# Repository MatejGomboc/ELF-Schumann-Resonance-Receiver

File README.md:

# ELARA -- ELF Atmospheric Radio Analyser

A professional-grade electric-field receiver for natural ELF radio signals
(1--50 Hz), optimised for Schumann resonance monitoring with exceptional
sensitivity. Inspired by [Renato Romero's](http://www.vlf.it/cumiana/livedata.html)
electric-field receiver work, engineered for dramatically better noise
performance using modern electrometer-grade components.

## Architecture

The system is deliberately simplified: the only custom PCB is the outdoor
antenna unit. The indoor side is entirely off-the-shelf.

- **Marconi T-antenna** (~10 m vertical, ~15 m capacitive top, ~140 pF)
- **Outdoor unit** -- single custom PCB inside a compartmentalised ALU EM shield,
  housed in a weatherproof plastic enclosure, with a separate two-bucket PSU box
  and, on mains, a 30 W thermostat box heater that keeps the ADC within its rating
  in winter; the box stands on a stiff steel post at the foot of the down-lead under
  a white aluminium sun and rain roof on its own arms
- **Indoor unit** -- any USB audio interface with an AES3 input (or an S/PDIF input
  through a 110 ohm to 75 ohm balun), connected to a PC

Both cables (AES3 digital audio on shielded Cat5e/6 with an RJ45, and the
screened 230 V AC mains cable) use "reverse shielding" --
the shields contain the cables' own emissions to protect the antenna, not the
other way around.

## Signal Chain

| Stage | Component | Key Spec |
| --- | --- | --- |
| Input RF filter | 2-stage RC (air-gap plate caps, 50 pF each) | fc ~96.5 kHz, FM -121 dB, AM -41 dB |
| Electrometer preamp | LMP7721 (40 dB ELF bandpass gain) | 6.5 nV/sqrt(Hz), 0.01 fA/sqrt(Hz) |
| Guard ring driver | LMP7715 | Drives active guard on all PCB layers |
| Antenna bias | LMP7715 (2.5V mid-supply via 47k divider) | Through a 1-100 Gohm glass resistor at J202 (100 Gohm recommended), soldered straight into the board; a clip lead across it resets the input at start-up |
| Anti-aliasing filter | Passive RC (10k + 100nF, C0G/NP0) | fc = 159 Hz |
| ADC driver | OPA388 (rail-to-rail input, unity gain) | 100 ohm + 2.7 nF C0G into the PCM1804 |
| ADC | PCM1804 (24-bit delta-sigma, stereo, 192 kHz) | 112 dB dynamic range |
| Digital output | CS8406 AES3 TX + S22083 transformer + shielded RJ45 | AES3 110 ohm on pins 4/5, galvanically isolated |
| Master clock | 24.576 MHz MEMS oscillator | Feeds both ADC and AES3 TX |
| Power supply | 6.98 V DC from the two-bucket PSU (or a battery up to 13 V) -> ADM7150 LDOs (5V analogue + 3.3V digital), about 100 mA; TPS3808 brown-out reset | 1.6 uV RMS noise |

## Preamp Topology

Non-inverting amplifier with bandpass gain and DC blocking:

```text
        Cf (15nF, C0G)
    +----||----+
    |  Rf=100k |
VOUT-+--/\/\/--+--IN-  (LMP7721)
                |
              Rg=1k
                |
            Cg=100uF (film, DC block)
                |
               GND
```

- **DC gain: 0 dB** -- Cg blocks DC, no offset amplification
- **ELF gain: 40 dB (100x)** -- flat across all 7 Schumann resonances (1.6--106 Hz)
- **Above 106 Hz: rolls off** -20 dB/dec towards unity (Cf shorts Rf)
- **Output coupling:** C_out (10uF film) blocks 2.5V DC to ADC
- **Max amplification is limited by 50 Hz mains E-field pickup** from nearby power
  lines. The input resistance is the 1-100 Gohm J202 bias resistor, far above the
  antenna's 23 Mohm at 50 Hz, so the antenna picks up 50 Hz with full efficiency.
  The 40 dB gain keeps worst-case 50 Hz within the linear range: 29.5 mV rms at the
  antenna before clipping (set by the preamp's output swing), 15.4 dB
  of headroom over 5 mV of pickup (`simulations/system`). A software notch filter
  removes 50 Hz cleanly.

## Noise Performance

At the 1st Schumann resonance (7.83 Hz) with a 140 pF antenna:

| | ELARA (LMP7721) | Romero LNVA (AD820) |
| --- | --- | --- |
| Noise at the amplifier input | 26.7 nV/sqrt(Hz) (behind the 0.583 cap divider) | ~121 nV/sqrt(Hz) |
| System noise (at antenna) | **45.8 nV/sqrt(Hz)** | ~121 nV/sqrt(Hz) |
| ADC noise floor, referred to the antenna | **0.7 nV/sqrt(Hz)** (41 nV/sqrt(Hz) at the ADC input) | N/A (analogue output) |
| FM rejection (100 MHz) | **-121 dB** (ideal RC; strays limit it to about -95 dB) | none |
| AM rejection (1 MHz) | **-41 dB** | none |
| Detection threshold | **0.0070 uV/m/sqrt(Hz)** | 0.0186 uV/m/sqrt(Hz) |
| Improvement | **2.6x voltage, 7x power** | baseline |

The ELARA figures are from the SPICE model (`simulations/spice`). The filter
resistors (2x 33k) dominate the noise budget: 48 % from the one next to the
amplifier and 26 % from the one at the antenna. The LMP7721's own voltage noise
adds 13 %, PCB leakage current 10 % and Rg 2 %. (The first Python budget, 64.6
nV/sqrt(Hz), was 3 dB pessimistic.) The recommended 100 Gohm J202 bias resistor
raises the floor to 74.8 nV/sqrt(Hz) at SR1, still 12.8 dB below the natural ELF
background. Everything after the preamp (driver, ADC, references) adds only
1.6-2.0 nV/sqrt(Hz) at the antenna, so the PCM1804 is transparent.

Expected Schumann resonance SNR (typical daytime conditions, 0.1 Hz bins, J202 =
100 Gohm; `simulations/system`):

| Mode | Frequency | SNR |
| --- | --- | --- |
| SR1 | 7.83 Hz | **38.8 dB** |
| SR2 | 14.3 Hz | **35.6 dB** |
| SR3 | 20.8 Hz | **33.5 dB** |
| SR7 | 45.0 Hz | **23.5 dB** |

## Stereo Noise Reference Channel

The PCM1804 is a stereo ADC. The right channel input (VINR) is tied to the
internal common-mode voltage (VCOMR), providing a **noise reference**. PC software
cross-correlates L and R channels: correlated noise is system noise (PSU, ADC
clock jitter, ground loops), uncorrelated signal on L only is the antenna signal.
This enables real-time coherent noise subtraction.

## No Input Protection -- By Design

There is deliberately no ESD or overvoltage protection on the antenna input. Any
protection component would introduce leakage currents that destroy the
femtoampere-level noise floor. Protection and electrometer-grade sensitivity are
fundamentally incompatible.

**Disconnect the antenna during thunderstorms.**

## Target Specifications

| Parameter | Value |
| --- | --- |
| Frequency range | 1--50 Hz (ELF, Schumann resonances) |
| Preamp gain | 40 dB (100x) flat across ELF band |
| System noise floor @ 7.83 Hz | 45.8 nV/sqrt(Hz) at the antenna (SPICE); 74.8 with the 100 Gohm bias resistor |
| ADC dynamic range | 112 dB (PCM1804) |
| ADC resolution | 24-bit, 192 kHz |
| Digital output | AES3 (110 ohm) on an RJ45 for shielded Cat5e/6 |
| Cable length | Up to 100 m (AES3, transformer-isolated) |
| Power (outdoor unit) | 6.98 V DC (two-bucket PSU) or a battery up to 13 V (6.98-13 V input) -> ADM7150 LDOs (5V + 3.3V), about 100 mA |
| Guard ring | LMP7715 active guard (83x leakage reduction) |
| FM rejection | -121 dB at 100 MHz (ideal RC; about -95 dB with strays) |
| AM rejection | -41 dB at 1 MHz |

## Repo Structure

```text
PCB/
  antenna_amplifier/   KiCad 9 project -- main outdoor unit (design.py -> schematic, layout.py -> PCB)
  acdc_converter/      KiCad 9 project -- two-bucket isolated PSU (design.py, layout.py)
  plate_capacitor/     64 x 64 mm air-gap capacitor plate (layout.py)
  elara.pretty/        project footprints (PTFE input turret, Newava S22083 transformer, strip holes)
  elara.3dshapes/      3D models for parts KiCad has none for (tools/models3d.py)
  */fab/               Gerbers + drill (JLCPCB zip), pick-and-place, BOM, PDFs, 3D render,
                       populated STEP, interactive HTML BOM
simulations/
  preamp_noise/        LMP7721 noise analysis vs AD820/ADA4530-1/OP27
  signal_chain/        Feedback gain analysis, expected Schumann signal levels
  input_filter/        Filter R optimisation, RC cascade Bode plot
  antenna/             Antenna capacitance & signal loss tradeoff
  plate_capacitor/     Air-gap capacitor geometry calculator
  spice/               ngspice front-end AC/noise model, antenna bias resistor trade-off
  psu/                 Two-bucket PSU: dropout, swap artefacts, cold start, 50 Hz leakage
  stability/           Phase margin of every op-amp stage
  system/              End-to-end noise, headroom and Schumann SNR budget
  em/                  Plate-capacitor field solve, shielding, guard and digital coupling
  thermal/             Both boards and the outdoor box in an east Slovenian climate
  mechanics/           Board and plate modes, plate-capacitor clamp, microphonics, wind
software/elara/        PC software: capture, decimation, mains canceller, Schumann fit
mechanical/            CadQuery shield, PSU box, plate-cap assembly, outer box (STEP/DXF)
bom/                   Priced BOM (build_bom.py) and cost-down options
datasheets/ds2sf/      Datasheet pin extractions (Adom DS2SF) behind tools/pin_audit.py
.claude/skills/        Claude Code skills for this repo (design flow, pin audit, docs sync,
                       env setup, skill upkeep)
.github/workflows/     CI: every design check on each push; release packages on v* tags
tools/
  kicadgen/            KiCad 9 schematic/PCB generators, netlist check, Freerouting driver
  fab_outputs.sh       Fabrication package per board
  ibom.py              Interactive HTML BOM (InteractiveHtmlBom, headless)
  pin_audit.py         Every IC's pins and nets against its manufacturer datasheet
  branch_docs.py       The documents agree on the working branch (fails a merge into master until updated)
  check_all.sh         All design checks in one go
  setup_env.sh         KiCad 9, ngspice, Freerouting and the .venv on a fresh Ubuntu 24.04
  route_psu.sh         Place, route (with the isolation barrier) and finish the PSU board
  mains_clearance.py   PSU mains creepage / clearance check
  fp_variants.py       Footprint variants (no silk on the guard island, mains terminal pads)
  models3d.py          3D models (STEP) into PCB/elara.3dshapes/
  normalise_outputs.py Reverts regenerated outputs whose only change is metadata
images/                Matplotlib-generated SVG diagrams
```

## Project Status

Revision 0.2 on the `master` branch is ready for fabrication. It has:

- generated schematics, netlist-checked and ERC clean
- all three boards routed, with 0 DRC errors and 0 unconnected items, and fab packages
- simulations, mechanics with a clash check, PC software and a priced BOM
- a PSU with an EDLC overvoltage crowbar and a GDT across its isolation barrier, and
  a mains-side box heater for winter
- an outdoor box on a stiff post in a field under a centred 500 x 500 mm shade roof
  (every thermal design verdict passes, the EDLCs at most 63.7 C on a record 40 C day)
- one check script (`tools/check_all.sh`, also run in CI): netlists, ERC, schematic
  legibility, DRC with parity, mains clearances, fit check, pin audit, branch model
  in the documents and the software tests

What remains to check before ordering is listed in [STATUS.md](STATUS.md).
[ASSEMBLY.md](ASSEMBLY.md) covers hand assembly and bring-up of the boards,
[MOUNTING.md](MOUNTING.md) the mechanical build, site and earthing, and
[MAINS_CABLE.md](MAINS_CABLE.md) the shielded mains feed. Ordering is in
[bom/ORDERING.md](bom/ORDERING.md) (Farnell, Mouser and Digi-Key upload files), and
local mechanical suppliers in [mechanical/SUPPLIERS_SI.md](mechanical/SUPPLIERS_SI.md).
[PLAN.md](PLAN.md) section 0 lists the rev 0.2 design changes.

## Toolchain

| Tool | Purpose |
| --- | --- |
| KiCad 9.0 | Schematic, PCB layout, component libraries |
| Python + numpy/scipy/matplotlib | Noise modelling, signal analysis, simulations |
| CadQuery (Python) | 3D models (STEP) for components and enclosure |
| tools/kicadgen | Generated schematics and boards, netlist check, Freerouting 1.9 driver |
| Freerouting 1.9 | Autorouter (batch mode, needs an X display, e.g. Xvfb) |
| [Adom DS2SF](https://wiki.adom.inc/adom/adom-ds2sf) | Datasheet PDF to pin table with the page each pin was read from; feeds `tools/pin_audit.py` |

Other AI-assisted EDA tools worth a look are in the [Adom apps catalogue](https://wiki.adom.inc/apps):
KiCad Bridge (an AI driving a desktop KiCad on Windows), Concur (cross-checks KiCad, Altium
and EAGLE libraries against a datasheet extraction), adom-lbr (library conversion) and
JLCPCB / Mouser / DigiKey part searches.

## Licence

This project is licensed under the **CERN Open Hardware Licence v2 -- Weakly
Reciprocal (CERN-OHL-W-2.0)**.

See [LICENCE](./LICENCE) for full terms.

Copyright 2025-2026 [MatejGomboc](https://github.com/MatejGomboc/ELF-Schumann-Resonance-Receiver)

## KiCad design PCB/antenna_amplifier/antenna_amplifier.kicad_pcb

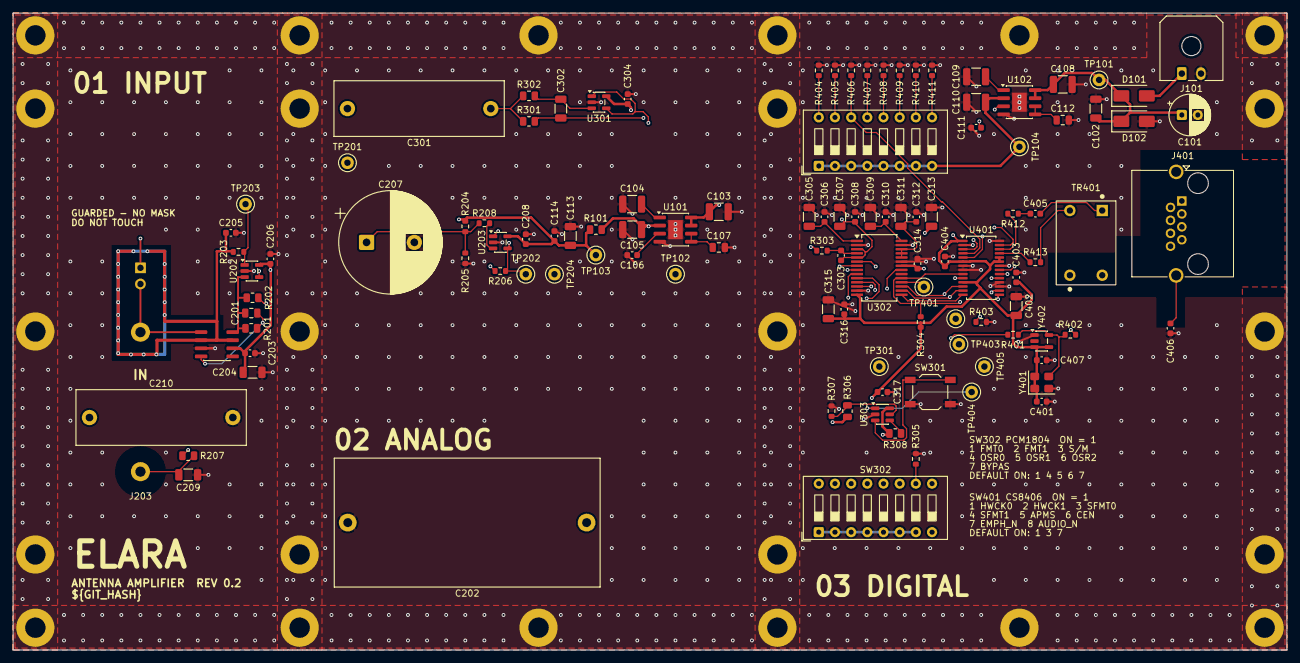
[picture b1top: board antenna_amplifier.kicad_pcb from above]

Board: 4 copper layers, 200.0 x 100.0 mm, 138 parts (0 on the bottom side), 66 nets.

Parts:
C101: 100u; CP_Radial_D6.3mm_P2.50mm
C102, C204, C305, C307, C309, C311, C313, C315, C402: 10u; C_1206_3216Metric
C103, C104, C105, C108, C109, C110: 22u; C_1210_3225Metric
C106, C111: 1u; C_0603_1608Metric
C107, C112: 2.2u; C_0805_2012Metric
C113: 22u; C_1206_3216Metric
C114, C203, C206, C208, C304, C306, C308, C310, C312, C314, C316, C317, C401, C403, C404, C405, C407: 100n; C_0603_1608Metric
C201: 15n; C_0805_2012Metric
C202: 100u; C_Rect_L41.5mm_W20.0mm_P37.50mm_MKS4
C205: 220p; C_0603_1608Metric
C207: 4700u; CP_Radial_D16.0mm_P7.50mm
C209, C302: 100n; C_1206_3216Metric
C210, C301: 10u; C_Rect_L26.5mm_W8.5mm_P22.50mm_MKS4
C303: 2.7n; C_0603_1608Metric
C406: 10n; C_0603_1608Metric
D101: SS34; D_SMA
D102: SMAJ13A; D_SMA
H1, H2, H3, H4, H5, H6, H7, H8, H9, H10, H11, H12, H13, H14, H15, H16, H17, H18, H19, H20, H21, H22, H23, H24: M3; MountingHole_M3_Strip
J101: DC IN; Molex_Micro-Fit_3.0_43650-0200_1x02_P3.00mm_Horizontal
J201: FILT_IN; Turret_PTFE_D3.0mm_Drill1.6mm
J202: BIAS; PinHeader_1x02_P2.54mm_Vertical_NoSilk
J203: PLATE_RET; Turret_PTFE_D3.0mm_Drill1.6mm
J401: AES3 OUT; RJ45_Amphenol_RJHSE5380
R101: 10; R_0805_2012Metric
R201, R207, R306, R308: 100k; R_0805_2012Metric
R202: 1k; R_0805_2012Metric
R203: 470; R_0603_1608Metric
R204, R205, R305, R403, R404, R405, R406, R407, R408, R409, R410, R411: 47k; R_0603_1608Metric
R206: 1k; R_0603_1608Metric
R208, R304: 10k; R_0603_1608Metric
R301: 47k; R_0805_2012Metric
R302: 10k; R_0805_2012Metric
R303: 100; R_0603_1608Metric
R307: 9.53k; R_0603_1608Metric
R401, R402: 33; R_0603_1608Metric
R412, R413: 22; R_0603_1608Metric
SW301: RESET; SW_SPST_TL3342
SW302: PCM1804 MODE; SW_DIP_SPSTx08_Slide_9.78x22.5mm_W7.62mm_P2.54mm
SW401: CS8406 MODE; SW_DIP_SPSTx08_Slide_9.78x22.5mm_W7.62mm_P2.54mm
TP101: +9V; TestPoint_Keystone_5000-5004_Miniature
TP102: +5VA; TestPoint_Keystone_5000-5004_Miniature
TP103: +5V_PRE; TestPoint_Keystone_5000-5004_Miniature
TP104: +3V3; TestPoint_Keystone_5000-5004_Miniature
TP201: PREAMP_OUT; TestPoint_Keystone_5000-5004_Miniature
TP202: BIAS_BUF; TestPoint_Keystone_5000-5004_Miniature
TP203: GUARD_DRV; TestPoint_Keystone_5000-5004_Miniature
TP204, TP405: GND; TestPoint_Keystone_5000-5004_Miniature
TP301: OVFL; TestPoint_Keystone_5000-5004_Miniature
TP401: MCLK_ADC; TestPoint_Keystone_5000-5004_Miniature
TP402: BCK; TestPoint_Keystone_5000-5004_Miniature
TP403: LRCK; TestPoint_Keystone_5000-5004_Miniature
TP404: RESET_N; TestPoint_Keystone_5000-5004_Miniature
TR401: S22083; Transformer_Newava_S22083
U101: ADM7150ARDZ-5.0; SOIC-8-1EP_3.9x4.9mm_P1.27mm_EP2.29x3mm
U102: ADM7150ARDZ-3.3; SOIC-8-1EP_3.9x4.9mm_P1.27mm_EP2.29x3mm
U201: LMP7721; SOIC-8_3.9x4.9mm_P1.27mm_GuardIsland
U202, U203: LMP7715; SOT-23-5
U301: OPA388; SOT-23-5
U302: PCM1804; SSOP-28_5.3x10.2mm_P0.65mm
U303: TPS3808G01; SOT-23-6
U401: CS8406; TSSOP-28_4.4x9.7mm_P0.65mm
Y401: 24.576MHz; Oscillator_SMD_SiT_PQFN-4Pin_3.2x2.5mm
Y402: 24.576MHz; SOT-23-5

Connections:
+3V3: C110.1, C315.1, C316.1, C317.1, C401.1, C402.1, C403.1, C404.1, C407.1, R304.1, R308.1, SW302.1, SW302.2, SW302.3, SW302.4, SW302.5, SW302.6, SW302.7, SW401.1, SW401.2, SW401.3, SW401.4, SW401.5, SW401.6, SW401.7, SW401.8, TP104.1, U102.2, U302.14, U303.6, U401.1, U401.6, U401.11, U401.23, U401.24, Y401.1, Y401.4, Y402.3, Y402.4
+5VA: C105.1, C304.1, C313.1, C314.1, R101.1, R306.1, TP102.1, U101.2, U301.5, U302.22
+5V_PRE: C113.1, C114.1, C203.1, C204.1, C206.1, C208.1, R101.2, R204.1, TP103.1, U201.6, U202.5, U203.5
+9V: C101.1, C102.1, C103.1, C108.1, D101.1, D102.1, TP101.1, U101.7, U101.8, U102.7, U102.8
/ADC (PCM1804)/ADC_A: C301.2, R301.1, R302.1
/ADC (PCM1804)/BYPAS: R305.1, SW302.10, U302.12
/ADC (PCM1804)/DRV_OUT: R303.1, U301.1, U301.4
/ADC (PCM1804)/FMT0: SW302.16, U302.6
/ADC (PCM1804)/FMT1: SW302.15, U302.7
/ADC (PCM1804)/MR_N: SW301.1, U303.3
/ADC (PCM1804)/OSR0: SW302.13, U302.9
/ADC (PCM1804)/OSR1: SW302.12, U302.10
/ADC (PCM1804)/OSR2: SW302.11, U302.11
/ADC (PCM1804)/OVFL: TP301.1, U302.21
/ADC (PCM1804)/RST_CT: R308.2, U303.4
/ADC (PCM1804)/RST_SENSE: R306.2, R307.1, U303.5
/ADC (PCM1804)/SM: SW302.14, U302.8
/ADC (PCM1804)/VCOML: C302.2, C303.2, C307.1, C308.1, R301.2, U302.3, U302.5
/ADC (PCM1804)/VCOMR: C311.1, C312.1, U302.24, U302.25, U302.26
/ADC (PCM1804)/VINL: C303.1, R303.2, U302.4
/ADC (PCM1804)/VINL_F: C302.1, R302.2, U301.3
/ADC (PCM1804)/VREFL: C305.1, C306.1, U302.1
/ADC (PCM1804)/VREFR: C309.1, C310.1, U302.28
/Clock and AES3 output/AES_A: C405.1, R412.2
/Clock and AES3 output/AES_COLD: J401.5, TR401.4
/Clock and AES3 output/AES_HOT: J401.4, TR401.3
/Clock and AES3 output/AES_P1: C405.2, TR401.1
/Clock and AES3 output/AES_P2: R413.1, TR401.2
/Clock and AES3 output/AES_SHIELD: C406.1, J401.SH
/Clock and AES3 output/APMS: R408.1, SW401.12, U401.10
/Clock and AES3 output/AUDIO_N: R411.1, SW401.9, U401.19
/Clock and AES3 output/CEN: R409.1, SW401.11, U401.16
/Clock and AES3 output/EMPH_N: R410.1, SW401.10, U401.3
/Clock and AES3 output/HWCK0: R404.1, SW401.16, U401.20
/Clock and AES3 output/HWCK1: R405.1, SW401.15, U401.27
/Clock and AES3 output/MCLK_TX: R402.2, U401.21
/Clock and AES3 output/OSC_OUT: R401.1, R402.1, Y401.3, Y402.5
/Clock and AES3 output/SFMT0: R406.1, SW401.14, U401.4
/Clock and AES3 output/SFMT1: R407.1, SW401.13, U401.5
/Clock and AES3 output/TCBL: R403.1, U401.15
/Clock and AES3 output/TXN: R413.2, U401.25
/Clock and AES3 output/TXP: R412.1, U401.26
/Electrometer front end/ANT_BIAS: J202.1, R206.2
/Electrometer front end/BIAS_BUF: R206.1, R207.1, TP202.1, U203.1, U203.4
/Electrometer front end/BIAS_DIV: C207.1, R204.2, R205.1, R208.1
/Electrometer front end/BIAS_IN: R208.2, U203.3
/Electrometer front end/CG: C202.1, R202.2
/Electrometer front end/GUARD: C205.1, R203.2, U201.2, U201.7
/Electrometer front end/GUARD_DRV: R203.1, TP203.1, U202.1, U202.4
/Electrometer front end/IN_N: C201.1, R201.1, R202.1, U201.8, U202.3
/Electrometer front end/IN_P: J201.1, J202.2, U201.1
/Electrometer front end/PLATE_RET: C209.1, C210.1, J203.1, R207.2
/Power input and regulators/BYP_A: C106.1, U101.3
/Power input and regulators/BYP_D: C111.1, U102.3
/Power input and regulators/REF_A: C107.1, U101.5, U101.6
/Power input and regulators/REF_D: C112.1, U102.5, U102.6
/Power input and regulators/VIN_RAW: D101.2, J101.1
/Power input and regulators/VREG_A: C104.1, U101.1
/Power input and regulators/VREG_D: C109.1, U102.1
BCK: TP402.1, U302.16, U401.13
GND: C101.2, C102.2, C103.2, C104.2, C105.2, C106.2, C107.2, C108.2, C109.2, C110.2, C111.2, C112.2, C113.2, C114.2, C202.2, C203.2, C204.2, C205.2, C206.2, C207.2, C208.2, C209.2, C210.2, C304.2, C305.2, C306.2, C307.2, C308.2, C309.2, C310.2, C311.2, C312.2, C313.2, C314.2, C315.2, C316.2, C317.2, C401.2, C402.2, C403.2, C404.2, C406.2, C407.2, D102.2, H1.1, H2.1, H3.1, H4.1, H5.1, H6.1, H7.1, H8.1, H9.1, H10.1, H11.1, H12.1, H13.1, H14.1, H15.1, H16.1, H17.1, H18.1, H19.1, H20.1, H21.1, H22.1, H23.1, H24.1, J101.2, R205.2, R305.2, R307.2, R403.2, R404.2, R405.2, R406.2, R407.2, R408.2, R409.2, R410.2, R411.2, SW301.2, TP204.1, TP405.1, U101.4, U101.9, U102.4, U102.9, U201.3, U202.2, U203.2, U301.2, U302.2, U302.13, U302.23, U302.27, U303.2, U401.2, U401.7, U401.8, U401.17, U401.18, U401.22, U401.28, Y401.2, Y402.1
LRCK: TP403.1, U302.17, U401.12
MCLK_ADC: R401.2, TP401.1, U302.18
PREAMP_OUT: C201.2, C301.1, R201.2, TP201.1, U201.4
RESET_N: R304.2, TP404.1, U302.19, U303.1, U401.9
SDATA: U302.15, U401.14

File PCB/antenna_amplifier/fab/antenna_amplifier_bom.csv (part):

"Reference","Value","Footprint","Manufacturer","MPN","Description","QUANTITY","DNP"
"C101","100u","Capacitor_THT:CP_Radial_D6.3mm_P2.50mm","Panasonic","EEU-FR1E101","Electrolytic 100u 25V low-ESR, D6.3 P2.5","1",""
"C102,C204,C305,C309,C313,C315,C402","10u","Capacitor_SMD:C_1206_3216Metric","Murata","GRM31CR71E106KA12L","MLCC 10u 25V X7R 1206 (decoupling)","7",""
"C103-C105,C108-C110","22u","Capacitor_SMD:C_1210_3225Metric","Murata","GRM32ER71E226KE15L","MLCC 22u 25V X7R 1210 (ADM7150: >= 7 uF effective after DC bias)","6",""
"C106,C111","1u","Capacitor_SMD:C_0603_1608Metric","Murata","GRM188R71E105KA12D","MLCC 1u 25V X7R 0603 (decoupling)","2",""
"C107,C112","2.2u","Capacitor_SMD:C_0805_2012Metric","Murata","GRM21BR71E225KA73L","MLCC 2.2u 25V X7R 0805 (ADM7150 REF: >= 0.7 uF effective)","2",""
"C113","22u","Capacitor_SMD:C_1206_3216Metric","Murata","GRM31CR61C226ME15L","MLCC 22u 16V X5R 1206 (decoupling)","1",""
"C114,C203,C206,C208,C304,C306,C308,C310,C312,C314,C316,C317,C401,C403-C405,C407","100n","Capacitor_SMD:C_0603_1608Metric","Murata","GRM188R71H104KA93D","MLCC 100n 50V X7R 0603 (decoupling)","17",""
"C201","15n","Capacitor_SMD:C_0805_2012Metric","Murata","GRM2195C1H153JA01D","MLCC 15n 50V C0G 0805 (Cf, signal path)","1",""
"C202","100u","Capacitor_THT:C_Rect_L41.5mm_W20.0mm_P37.50mm_MKS4","WIMA","MKS4C061007G00KSSD","Film 100u 63 VDC PET, PCM 37.5 mm, 41.5 x 20 x 39.5 mm (Cg)","1",""
"C205","220p","Capacitor_SMD:C_0603_1608Metric","Murata","GRM1885C1H221JA01D","MLCC 220p 50V C0G 0603 (guard stability)","1",""
"C207","4700u","Capacitor_THT:CP_Radial_D16.0mm_P7.50mm","Panasonic","EEU-FR1C472","Electrolytic 4700u 16V, D16 P7.5 (bias divider filter)","1",""
"C209,C302","100n","Capacitor_SMD:C_1206_3216Metric","Murata","GRM31C5C1H104JA01L","MLCC 100n 50V C0G 1206 (signal path)","2",""
"C210,C301","10u","Capacitor_THT:C_Rect_L26.5mm_W8.5mm_P22.50mm_MKS4","WIMA","MKS4C051005F00KSSD","Film 10u 63 VDC PET, PCM 22.5 mm, 26.5 x 8.5 x 18.5 mm (C_out)","2",""
"C303","2.7n","Capacitor_SMD:C_0603_1608Metric","Murata","GRM1885C1H272JA01D","MLCC 2n7 50V C0G 0603 (ADC charge reservoir)","1",""
"D101","SS34","Diode_SMD:D_SMA","Vishay","SS34-E3/57T","Schottky 3 A 40 V, reverse-polarity protection","1",""
"D102","SMAJ13A","Diode_SMD:D_SMA","Littelfuse","SMAJ13A","TVS 13 V standoff unidirectional (VBR 14.4-15.9 V), input surge clamp","1",""
"J101","DC IN","Connector_Molex:Molex_Micro-Fit_3.0_43650-0200_1x02_P3.00mm_Horizontal","Molex","43650-0200","Micro-Fit 3.0 2-pin right-angle header, DC in: 6.98 V from the PSU or a 9-13 V battery","1",""
"J201","FILT_IN","elara:Turret_PTFE_D3.0mm_Drill1.6mm","-","PTFE press-fit turret or direct wire","Input from air-mounted RC filter (node 2), enters from the PCB bottom","1",""
"J202","BIAS","elara:PinHeader_1x02_P2.54mm_Vertical_NoSilk","-","no header: bias resistor leads soldered in the holes","Bias link: NO pin header (its plastic body leaks in the G-ohm range, across the bias resistor); solder the 1-100 G glass resistor straight into the two holes, standing off the board; reset = a clip lead across","1",""
"J203","PLATE_RET","elara:Turret_PTFE_D3.0mm_Drill1.6mm","-","PTFE press-fit turret or direct wire","Return of the plate capacitors' lower plates (was GND), enters from the PCB bottom through the second PTFE bush, beside the J201 lead","1",""
"J401","AES3 OUT","Connector_RJ:RJ45_Amphenol_RJHSE5380","Amphenol","RJHSE-5380","RJ45 8P8C shielded, right angle, no LEDs. AES3 on the blue pair: 4 hot, 5 cold (the same pair in T568A and T568B). Shell = cable shield, isolated from GND: it must not touch the shield wall","1",""
"R101","10","Resistor_SMD:R_0805_2012Metric","Panasonic","ERA-6AEB100V","Thin film 10R 0.1% 0805","1",""
"R201,R207,R306,R308","100k","Resistor_SMD:R_0805_2012Metric","Panasonic","ERA-6AEB104V","Thin film 100k 0.1% 25ppm 0805 (Rf)","4",""
"R202","1k","Resistor_SMD:R_0805_2012Metric","Panasonic","ERA-6AEB102V","Thin film 1k 0.1% 25ppm 0805 (Rg)","1",""
"R203","470","Resistor_SMD:R_0603_1608Metric","Panasonic","ERA-3AEB471V","Thin film 470R 0.1% 0603","1",""
"R204,R205","47k","Resistor_SMD:R_0603_1608Metric","Panasonic","ERA-3VRW4702V","Thin film 47k 0.05% 10ppm 0603 (bias divider)","2",""
"R206","1k","Resistor_SMD:R_0603_1608Metric","Panasonic","ERA-3AEB102V","Thin film 1k 0.1% 0603","1",""
"R208,R304","10k","Resistor_SMD:R_0603_1608Metric","Panasonic","ERA-3AEB103V","Thin film 10k 0.1% 0603","2",""
"R301","47k","Resistor_SMD:R_0805_2012Metric","Panasonic","ERA-6AEB473V","Thin film 47k 0.1% 25ppm 0805","1",""
"R302","10k","Resistor_SMD:R_0805_2012Metric","Panasonic","ERA-6AEB103V","Thin film 10k 0.1% 25ppm 0805 (R_AA)","1",""
"R303","100","Resistor_SMD:R_0603_1608Metric","Panasonic","ERA-3AEB101V","Thin film 100R 0.1% 0603","1",""
"R305,R403-R411","47k","Resistor_SMD:R_0603_1608Metric","Panasonic","ERA-3AEB473V","Thin film 47k 0.1% 0603 (mode-pin pull-down)","10",""
"R307","9.53k","Resistor_SMD:R_0603_1608Metric","Panasonic","ERA-3AEB9531V","Thin film 9.53k 0.1% 0603","1",""
"R401,R402","33","Resistor_SMD:R_0603_1608Metric","Panasonic","ERA-3AEB330V","Thin film 33R 0.1% 0603","2",""
"R412,R413","22","Resistor_SMD:R_0603_1608Metric","Vishay Dale","TNPW060322R0BEEA","Thin film 22R 0.1% 0603, anti-sulfur (AES3 source)","2",""
"SW301","RESET","Button_Switch_SMD:SW_SPST_TL3342","E-Switch","TL3342F160QG","Reset push button (ADC + AES3 TX)","1",""
"SW302","PCM1804 MODE","Button_Switch_THT:SW_DIP_SPSTx08_Slide_9.78x22.5mm_W7.62mm_P2.54mm","CTS","206-8ST","8-way DIP switch, PCM1804 mode pins","1",""
"SW401","CS8406 MODE","Button_Switch_THT:SW_DIP_SPSTx08_Slide_9.78x22.5mm_W7.62mm_P2.54mm","CTS","206-8ST","8-way DIP switch, CS8406 hardware-mode pins","1",""
"TP101","+9V","TestPoint:TestPoint_Keystone_5000-5004_Miniature","Keystone","5000","Test point +9V","1",""
"TP102","+5VA","TestPoint:TestPoint_Keystone_5000-5004_Miniature","Keystone","5000","Test point +5VA","1",""
"TP103","+5V_PRE","TestPoint:TestPoint_Keystone_5000-5004_Miniature","Keystone","5000","Test point +5V_PRE","1",""
"TP104","+3V3","TestPoint:TestPoint_Keystone_5000-5004_Miniature","Keystone","5000","Test point +3V3","1",""
"TP201","PREAMP_OUT","TestPoint:TestPoint_Keystone_5000-5004_Miniature","Keystone","5000","Test point PREAMP_OUT","1",""
"TP202","BIAS_BUF","TestPoint:TestPoint_Keystone_5000-5004_Miniature","Keystone","5000","Test point BIAS_BUF","1",""
"TP203","GUARD_DRV","TestPoint:TestPoint_Keystone_5000-5004_Miniature","Keystone","5000","Test point GUARD_DRV","1",""
"TP204,TP405","GND","TestPoint:TestPoint_Keystone_5000-5004_Miniature","Keystone","5001","Test point GND","2",""
"TP301","OVFL","TestPoint:TestPoint_Keystone_5000-5004_Miniature","Keystone","5000","Test point OVFL (high while the left channel clips)","1",""
"TP401","MCLK_ADC","TestPoint:TestPoint_Keystone_5000-5004_Miniature","Keystone","5000","Test point MCLK_ADC","1",""
"TP402","BCK","TestPoint:TestPoint_Keystone_5000-5004_Miniature","Keystone","5000","Test point BCK","1",""
"TP403","LRCK","TestPoint:TestPoint_Keystone_5000-5004_Miniature","Keystone","5000","Test point LRCK","1",""
"TP404","RESET_N","TestPoint:TestPoint_Keystone_5000-5004_Miniature","Keystone","5000","Test point RESET_N","1",""
"TR401","S22083","elara:Transformer_Newava_S22083","Newava","S22083","AES3 110 R pulse transformer 1:1, 2 kV isolation (4-pin, windings 1-2 / 3-4; pins per the Newava drawing: 10.16 x 5.08 mm)","1",""
"U101","ADM7150ARDZ-5.0","Package_SO:SOIC-8-1EP_3.9x4.9mm_P1.27mm_EP2.29x3mm","Analog Devices","ADM7150ARDZ-5.0-R7","Ultralow-noise LDO (1.6 uV rms), +5VA rail","1",""
"U102","ADM7150ARDZ-3.3","Package_SO:SOIC-8-1EP_3.9x4.9mm_P1.27mm_EP2.29x3mm","Analog Devices","ADM7150ARDZ-3.3-R7","Ultralow-noise LDO (1.6 uV rms), +3V3 rail","1",""
"U201","LMP7721","elara:SOIC-8_3.9x4.9mm_P1.27mm_GuardIsland","Texas Instruments","LMP7721MA/NOPB","Electrometer op-amp, 3 fA, inputs pins 1/8, guard pins 2/7","1",""
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
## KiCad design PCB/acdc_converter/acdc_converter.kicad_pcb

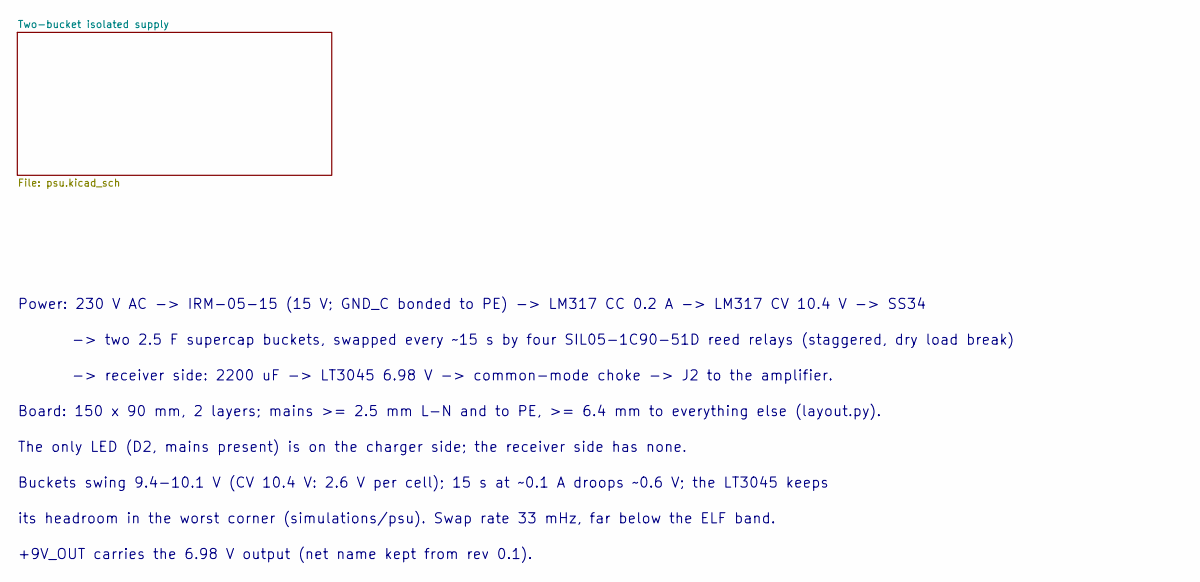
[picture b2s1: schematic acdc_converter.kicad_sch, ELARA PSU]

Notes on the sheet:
Power: 230 V AC -> IRM-05-15 (15 V; GND_C bonded to PE) -> LM317 CC 0.2 A -> LM317 CV 10.4 V -> SS34
-> two 2.5 F supercap buckets, swapped every ~15 s by four SIL05-1C90-51D reed relays (staggered, dry load break)
-> receiver side: 2200 uF -> LT3045 6.98 V -> common-mode choke -> J2 to the amplifier.
Board: 150 x 90 mm, 2 layers; mains >= 2.5 mm L-N and to PE, >= 6.4 mm to everything else (layout.py).
The only LED (D2, mains present) is on the charger side; the receiver side has none.
Buckets swing 9.4-10.1 V (CV 10.4 V: 2.6 V per cell); 15 s at ~0.1 A droops ~0.6 V; the LT3045 keeps
its headroom in the worst corner (simulations/psu). Swap rate 33 mHz, far below the ELF band.
+9V_OUT carries the 6.98 V output (net name kept from rev 0.1).

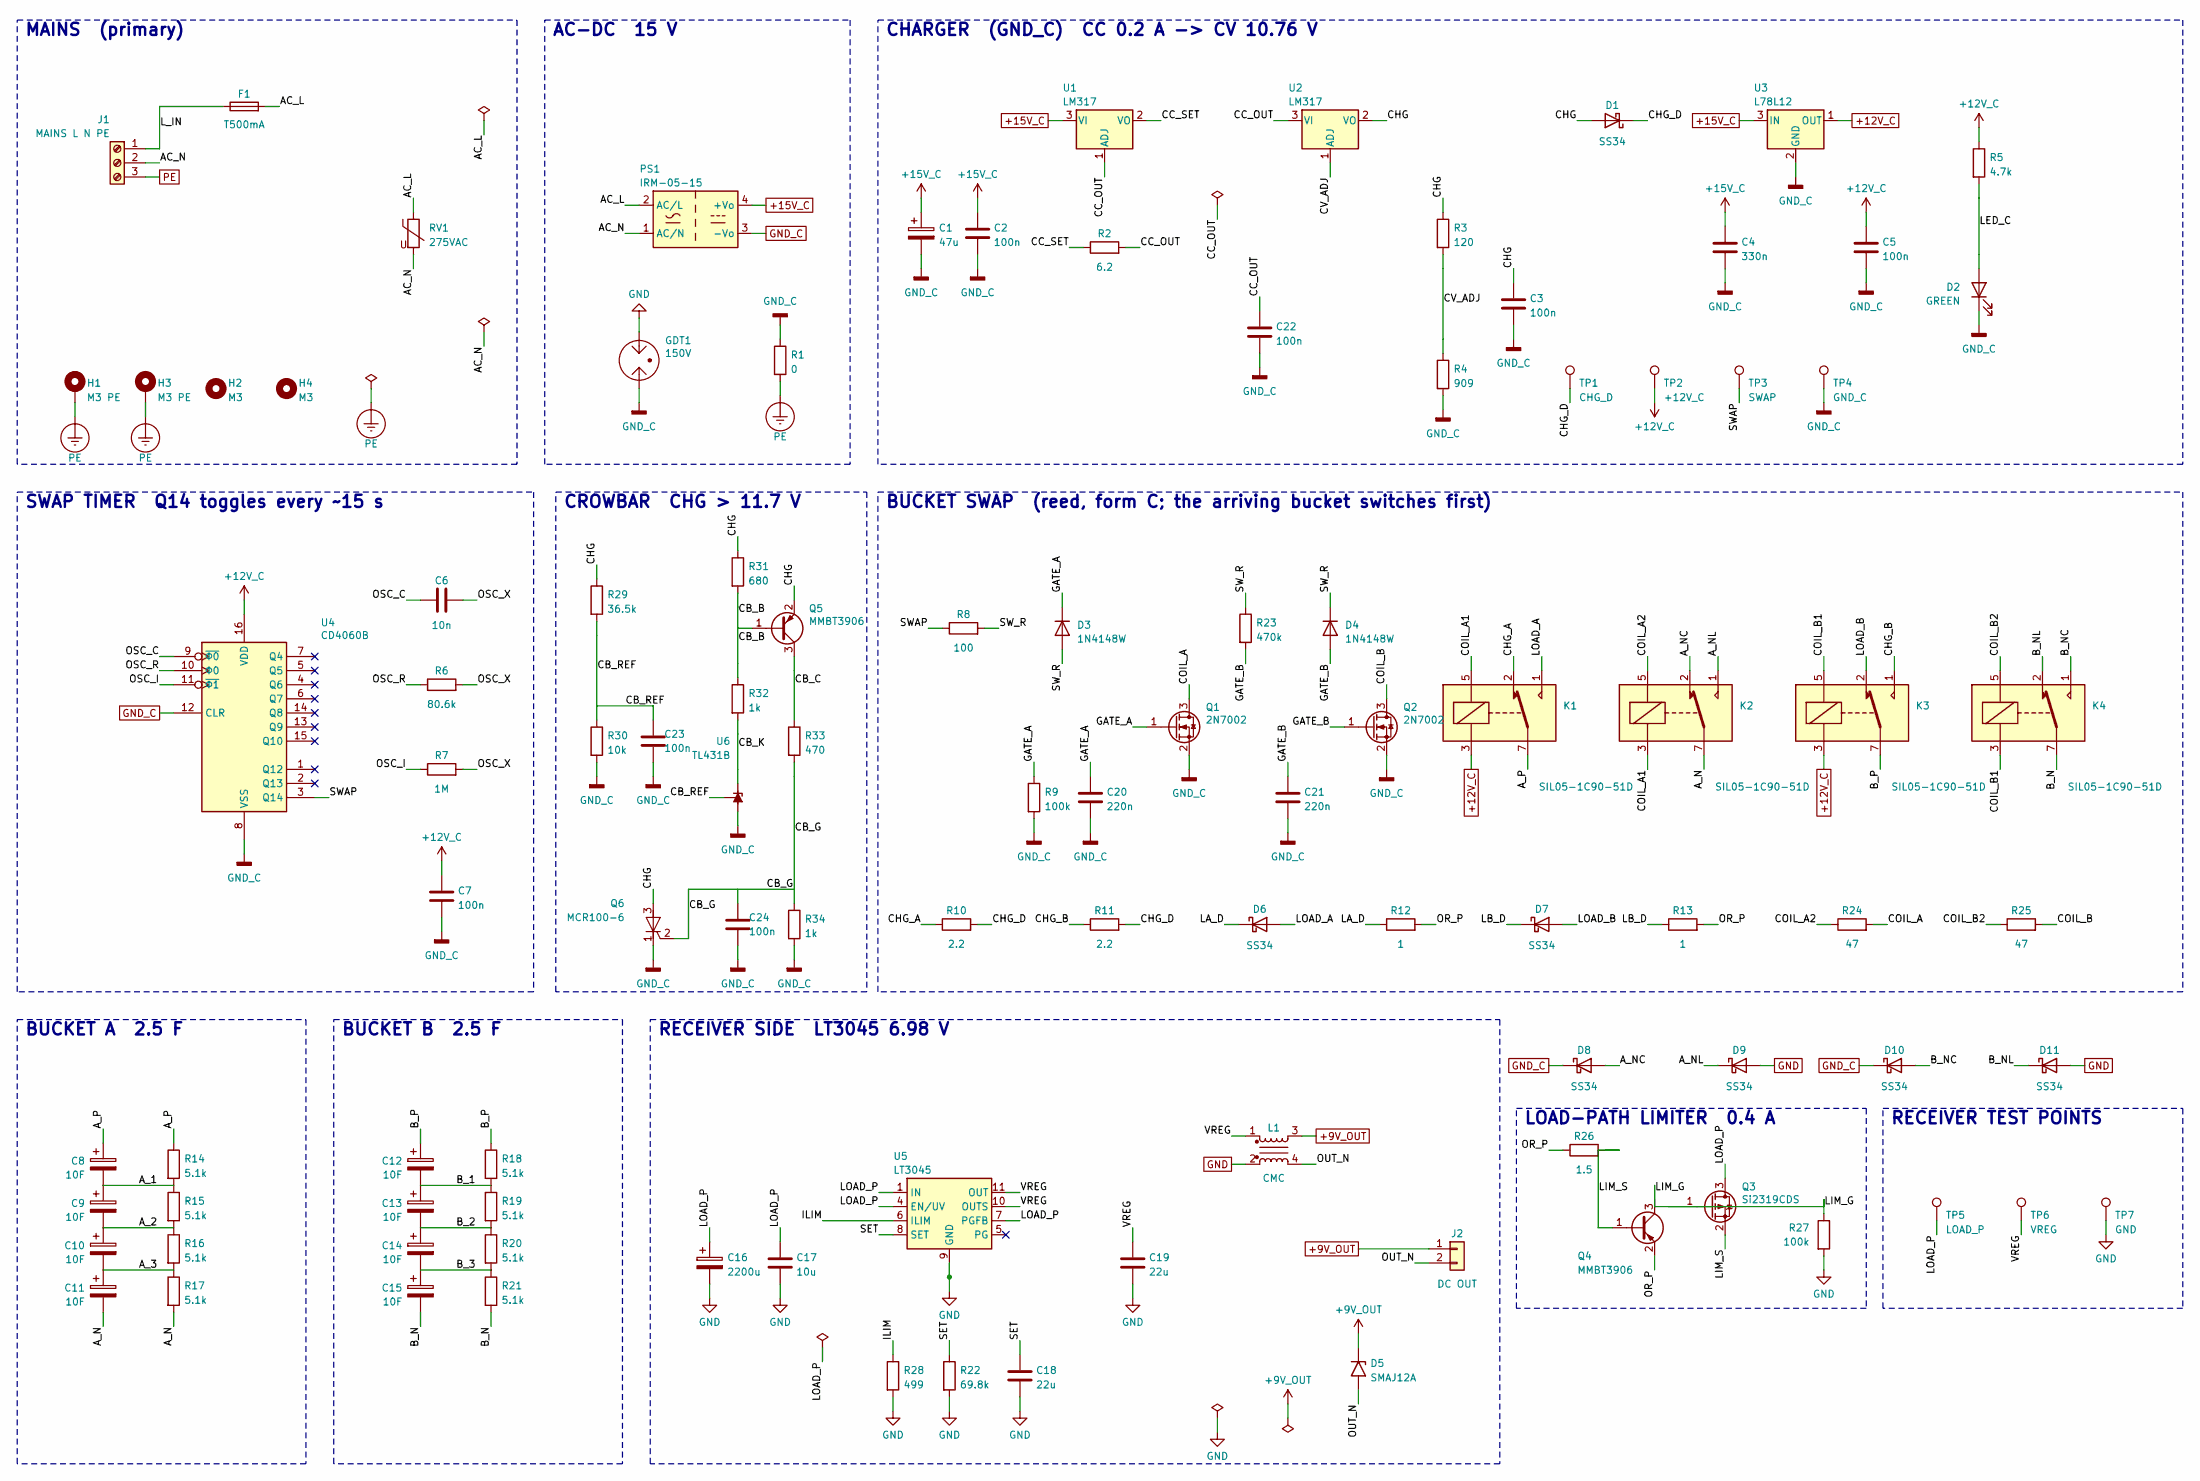
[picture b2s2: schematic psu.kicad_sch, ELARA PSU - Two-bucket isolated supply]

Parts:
C1: 47u; CP_Radial_D6.3mm_P2.50mm; MPN EEU-FR1E470
C2, C3, C5, C7, C22, C23, C24: 100n; C_0805_2012Metric; MPN GRM21BR71H104KA01L
C4: 330n; C_0805_2012Metric; MPN GRM21BR71H334KA88L
C6: 10n; C_0805_2012Metric; MPN GRM2195C1H103JA01D
C8, C9, C10, C11, C12, C13, C14, C15: 10F; CP_Radial_D12.5mm_P5.00mm; MPN HV1030-2R7106-R
C16: 2200u; CP_Radial_D12.5mm_P5.00mm; MPN EEU-FR1C222
C17: 10u; C_1206_3216Metric; MPN GRM31CR71E106KA12L
C18: 22u; C_1206_3216Metric; MPN GRM31CR71C226ME15L
C19: 22u; C_1210_3225Metric; MPN GRM32ER71E226KE15L
C20, C21: 220n; C_0805_2012Metric; MPN GRM21BR71H224KA01L
D1, D6, D7, D8, D9, D10, D11: SS34; D_SMA; MPN SS34-E3/57T
D2: GREEN; LED_0805_2012Metric; MPN 150080VS75000
D3, D4: 1N4148W; D_SOD-123; MPN 1N4148W-7-F
D5: SMAJ12A; D_SMA; MPN SMAJ12A
F1: T500mA; Fuseholder_Clip-5x20mm_Bel_FC-203-22_Lateral_P17.80x5.00mm_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; MPN 0215.500MXP + 2x FC-203-22 clips
GDT1: 150V; GDT_Bourns_2051; MPN 2051-15-SM-RPLF
H1, H3: M3 PE; MountingHole_3.2mm_M3_Pad_Via
H2, H4: M3; MountingHole_3.2mm_M3
J1: MAINS L N PE; TerminalBlock_Phoenix_MKDS-1,5-3-5.08_1x03_P5.08mm_Horizont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; MPN 1715734
J2: DC OUT; Molex_Micro-Fit_3.0_43650-0200_1x02_P3.00mm_Horizontal; MPN 43650-0200
K1, K2, K3, K4: SIL05-1C90-51D; Relay_SPDT_StandexMeder_SIL_Form1C; MPN SIL05-1C90-51D
L1: CMC; L_CommonModeChoke_Bourns_SRF1260; MPN SRF1260-102M
PS1: IRM-05-15; Converter_ACDC_MeanWell_IRM-05-xx_THT; MPN IRM-05-15
Q1, Q2: 2N7002; SOT-23; MPN 2N7002LT1G
Q3: Si2319CDS; SOT-23; MPN Si2319CDS-T1-GE3
Q4, Q5: MMBT3906; SOT-23; MPN MMBT3906LT1G
Q6: MCR100-6; TO-92; MPN MCR100-6G
R1: 0; R_1206_3216Metric; MPN ERJ-8GEY0R00V
R2: 6.2; R_2512_6332Metric; MPN CRCW25126R20FKEG
R3: 120; R_0805_2012Metric; MPN ERA-6AEB121V
R4: 909; R_1206_3216Metric; MPN ERA-8AEB9090V
R5: 4.7k; R_0805_2012Metric; MPN ERA-6AEB472V
R6: 80.6k; R_0805_2012Metric; MPN ERA-6AEB8062V
R7: 1M; R_0805_2012Metric; MPN ERA-6AEB105V
R8: 100; R_0805_2012Metric; MPN ERA-6AEB101V
R9, R27: 100k; R_0805_2012Metric; MPN ERA-6AEB104V
R10, R11: 2.2; R_2512_6332Metric; MPN CRCW25122R20FKEG
R12, R13: 1; R_2512_6332Metric; MPN CRCW25121R00FKEG
R14, R15, R16, R17, R18, R19, R20, R21: 5.1k; R_1206_3216Metric; MPN ERJ-8ENF5101V
R22: 69.8k; R_0805_2012Metric; MPN ERA-6AEB6982V
R23: 470k; R_0805_2012Metric; MPN ERJ-6ENF4703V
R24, R25: 47; R_0805_2012Metric; MPN ERJ-6ENF47R0V
R26: 1.5; R_2512_6332Metric; MPN CRCW25121R50FKEG
R28: 499; R_0805_2012Metric; MPN ERA-6AEB4990V
R29: 36.5k; R_0805_2012Metric; MPN ERA-6AEB3652V
R30: 10k; R_0805_2012Metric; MPN ERA-6AEB103V
R31: 680; R_0805_2012Metric; MPN ERJ-6ENF6800V
R32, R34: 1k; R_0805_2012Metric; MPN ERJ-6ENF1001V
R33: 470; R_0805_2012Metric; MPN ERJ-6ENF4700V
RV1: 275VAC; RV_Disc_D12mm_W4.7mm_P7.5mm; MPN B72210S0271K101
TP1: CHG_D; TestPoint_Keystone_5000-5004_Miniature; MPN 5000
TP2: +12V_C; TestPoint_Keystone_5000-5004_Miniature; MPN 5000
TP3: SWAP; TestPoint_Keystone_5000-5004_Miniature; MPN 5000
TP4: GND_C; TestPoint_Keystone_5000-5004_Miniature; MPN 5001
TP5: LOAD_P; TestPoint_Keystone_5000-5004_Miniature; MPN 5000
TP6: VREG; TestPoint_Keystone_5000-5004_Miniature; MPN 5000
TP7: GND; TestPoint_Keystone_5000-5004_Miniature; MPN 5001
U1, U2: LM317; TO-220-3_Horizontal_TabDown; MPN LM317BTG
U3: L78L12; SOT-89-3; MPN L78L12ABUTR
U4: CD4060B; SOIC-16_3.9x9.9mm_P1.27mm; MPN CD4060BM96
U5: LT3045; MSOP-12-1EP_3x4.039mm_P0.65mm_EP1.651x2.845mm; MPN LT3045EMSE#PBF
U6: TL431B; SOT-23; MPN TL431BIDBZR

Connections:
+9V_OUT: D5.1 (A1), J2.1, L1.3 (2)
+12V_C: C5.1, C7.1, K1.3, K3.3, R5.1, TP2.1, U3.1 (OUT), U4.16 (VDD)
+15V_C: C1.1, C2.1, C4.1, PS1.4 (+Vo), U1.3 (VI), U3.3 (IN)
/Two-bucket isolated supply/AC_L: F1.2, PS1.2 (AC/L), RV1.1
/Two-bucket isolated supply/AC_N: J1.2, PS1.1 (AC/N), RV1.2
/Two-bucket isolated supply/A_1: C8.2, C9.1, R14.2, R15.1
/Two-bucket isolated supply/A_2: C9.2, C10.1, R15.2, R16.1
/Two-bucket isolated supply/A_3: C10.2, C11.1, R16.2, R17.1
/Two-bucket isolated supply/A_N: C11.2, K2.7, R17.2
/Two-bucket isolated supply/A_NC: D8.2 (A), K2.2
/Two-bucket isolated supply/A_NL: D9.1 (K), K2.1
/Two-bucket isolated supply/A_P: C8.1, K1.7, R14.1
/Two-bucket isolated supply/B_1: C12.2, C13.1, R18.2, R19.1
/Two-bucket isolated supply/B_2: C13.2, C14.1, R19.2, R20.1
/Two-bucket isolated supply/B_3: C14.2, C15.1, R20.2, R21.1
/Two-bucket isolated supply/B_N: C15.2, K4.7, R21.2
/Two-bucket isolated supply/B_NC: D10.2 (A), K4.1
/Two-bucket isolated supply/B_NL: D11.1 (K), K4.2
/Two-bucket isolated supply/B_P: C12.1, K3.7, R18.1
/Two-bucket isolated supply/CB_B: Q5.1 (B), R31.2, R32.1
/Two-bucket isolated supply/CB_C: Q5.3 (C), R33.1
/Two-bucket isolated supply/CB_G: C24.1, Q6.2 (G), R33.2, R34.1
/Two-bucket isolated supply/CB_K: R32.2, U6.1 (K)
/Two-bucket isolated supply/CB_REF: C23.1, R29.2, R30.1, U6.2 (REF)
/Two-bucket isolated supply/CC_OUT: C22.1, R2.2, U1.1 (ADJ), U2.3 (VI)
/Two-bucket isolated supply/CC_SET: R2.1, U1.2 (VO)
/Two-bucket isolated supply/CHG: C3.1, D1.2 (A), Q5.2 (E), Q6.3 (A), R3.1, R29.1, R31.1, U2.2 (VO)
/Two-bucket isolated supply/CHG_A: K1.2, R10.1
/Two-bucket isolated supply/CHG_B: K3.1, R11.1
/Two-bucket isolated supply/CHG_D: D1.1 (K), R10.2, R11.2, TP1.1
/Two-bucket isolated supply/COIL_A: Q1.3 (D), R24.2
/Two-bucket isolated supply/COIL_A1: K1.5, K2.3
/Two-bucket isolated supply/COIL_A2: K2.5, R24.1
/Two-bucket isolated supply/COIL_B: Q2.3 (D), R25.2
/Two-bucket isolated supply/COIL_B1: K3.5, K4.3
/Two-bucket isolated supply/COIL_B2: K4.5, R25.1
/Two-bucket isolated supply/CV_ADJ: R3.2, R4.1, U2.1 (ADJ)
/Two-bucket isolated supply/GATE_A: C20.1, D3.1 (K), Q1.1 (G), R9.1
/Two-bucket isolated supply/GATE_B: C21.1, D4.2 (A), Q2.1 (G), R23.2
/Two-bucket isolated supply/ILIM: R28.1, U5.6 (ILIM)
/Two-bucket isolated supply/LA_D: D6.1 (K), R12.1
/Two-bucket isolated supply/LB_D: D7.1 (K), R13.1
/Two-bucket isolated supply/LED_C: D2.2 (A), R5.2
/Two-bucket isolated supply/LIM_G: Q3.1 (G), Q4.3 (C), R27.1
/Two-bucket isolated supply/LIM_S: Q3.2 (S), Q4.1 (B), R26.2
/Two-bucket isolated supply/LOAD_A: D6.2 (A), K1.1
/Two-bucket isolated supply/LOAD_B: D7.2 (A), K3.2
/Two-bucket isolated supply/LOAD_P: C16.1, C17.1, Q3.3 (D), TP5.1, U5.1 (IN), U5.2 (IN), U5.3 (IN), U5.4 (EN/UV), U5.7 (PGFB)
/Two-bucket isolated supply/L_IN: F1.1, J1.1
/Two-bucket isolated supply/OR_P: Q4.2 (E), R12.2, R13.2, R26.1
/Two-bucket isolated supply/OSC_C: C6.1, U4.9 (~Φ0)
/Two-bucket isolated supply/OSC_I: R7.1, U4.11 (~Φ1)
/Two-bucket isolated supply/OSC_R: R6.1, U4.10 (Φ0)
/Two-bucket isolated supply/OSC_X: C6.2, R6.2, R7.2
/Two-bucket isolated supply/OUT_N: D5.2 (A2), J2.2, L1.4
/Two-bucket isolated supply/SET: C18.1, R22.1, U5.8 (SET)
/Two-bucket isolated supply/SWAP: R8.1, TP3.1, U4.3 (Q14)
/Two-bucket isolated supply/SW_R: D3.2 (A), D4.1 (K), R8.2, R23.1
/Two-bucket isolated supply/VREG: C19.1, L1.1, TP6.1, U5.10 (OUTS), U5.11 (OUT), U5.12 (OUT)
GND: C16.2, C17.2, C18.2, C19.2, D9.2 (A), D11.2 (A), GDT1.3, L1.2 (3), R22.2, R27.2, R28.2, TP7.1, U5.9 (GND), U5.13 (GND)
GND_C: C1.2, C2.2, C3.2, C4.2, C5.2, C7.2, C20.2, C21.2, C22.2, C23.2, C24.2, D2.1 (K), D8.1 (K), D10.1 (K), GDT1.1, PS1.3 (-Vo), Q1.2 (S), Q2.2 (S), Q6.1 (K), R1.1, R4.2, R9.2, R30.2, R34.2, TP4.1, U3.2 (GND), U4.8 (VSS), U4.12 (CLR), U6.3 (A)
PE: H1.1, H3.1, J1.3, R1.2

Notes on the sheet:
MAINS (primary)
AC-DC 15 V
CHARGER (GND_C) CC 0.2 A -> CV 10.76 V
SWAP TIMER Q14 toggles every ~15 s
BUCKET SWAP (reed, form C; the arriving bucket switches first)
BUCKET A 2.5 F
BUCKET B 2.5 F
RECEIVER SIDE LT3045 6.98 V
LOAD-PATH LIMITER 0.4 A
RECEIVER TEST POINTS
CROWBAR CHG > 11.7 V

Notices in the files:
simulations/em/run_em.py:
SPDX-License-Identifier: CERN-OHL-W-2.0
Licence: CERN-OHL-W-2.0
PCB/antenna_amplifier/antenna_amplifier.kicad_pcb:
4 LAYER  1.6 MM  CERN-OHL-W-2.0
